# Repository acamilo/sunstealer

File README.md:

## SunStealer

Sunstealer is a 15 watt single color (rs485) networked LED strip built using a LT34781 driver and a PIC32MX110F016B. These strips are intended to be used to build larger LED panels with each strip covering a specific wavelength.

The goal is to be able to control the amount of light received by plants at each of these wavelengths and attempt to replicate some of the existing studies on type of light and it's affect on vegetative growth and fruiting.

There will be 5 variants of the strip each populated with LEDs targeting te following wavelengths (439,469,642,667,740) initially with the following ratios (1,1,2,2,1) This should make 1 105w LED light for hydro/aquaponics.

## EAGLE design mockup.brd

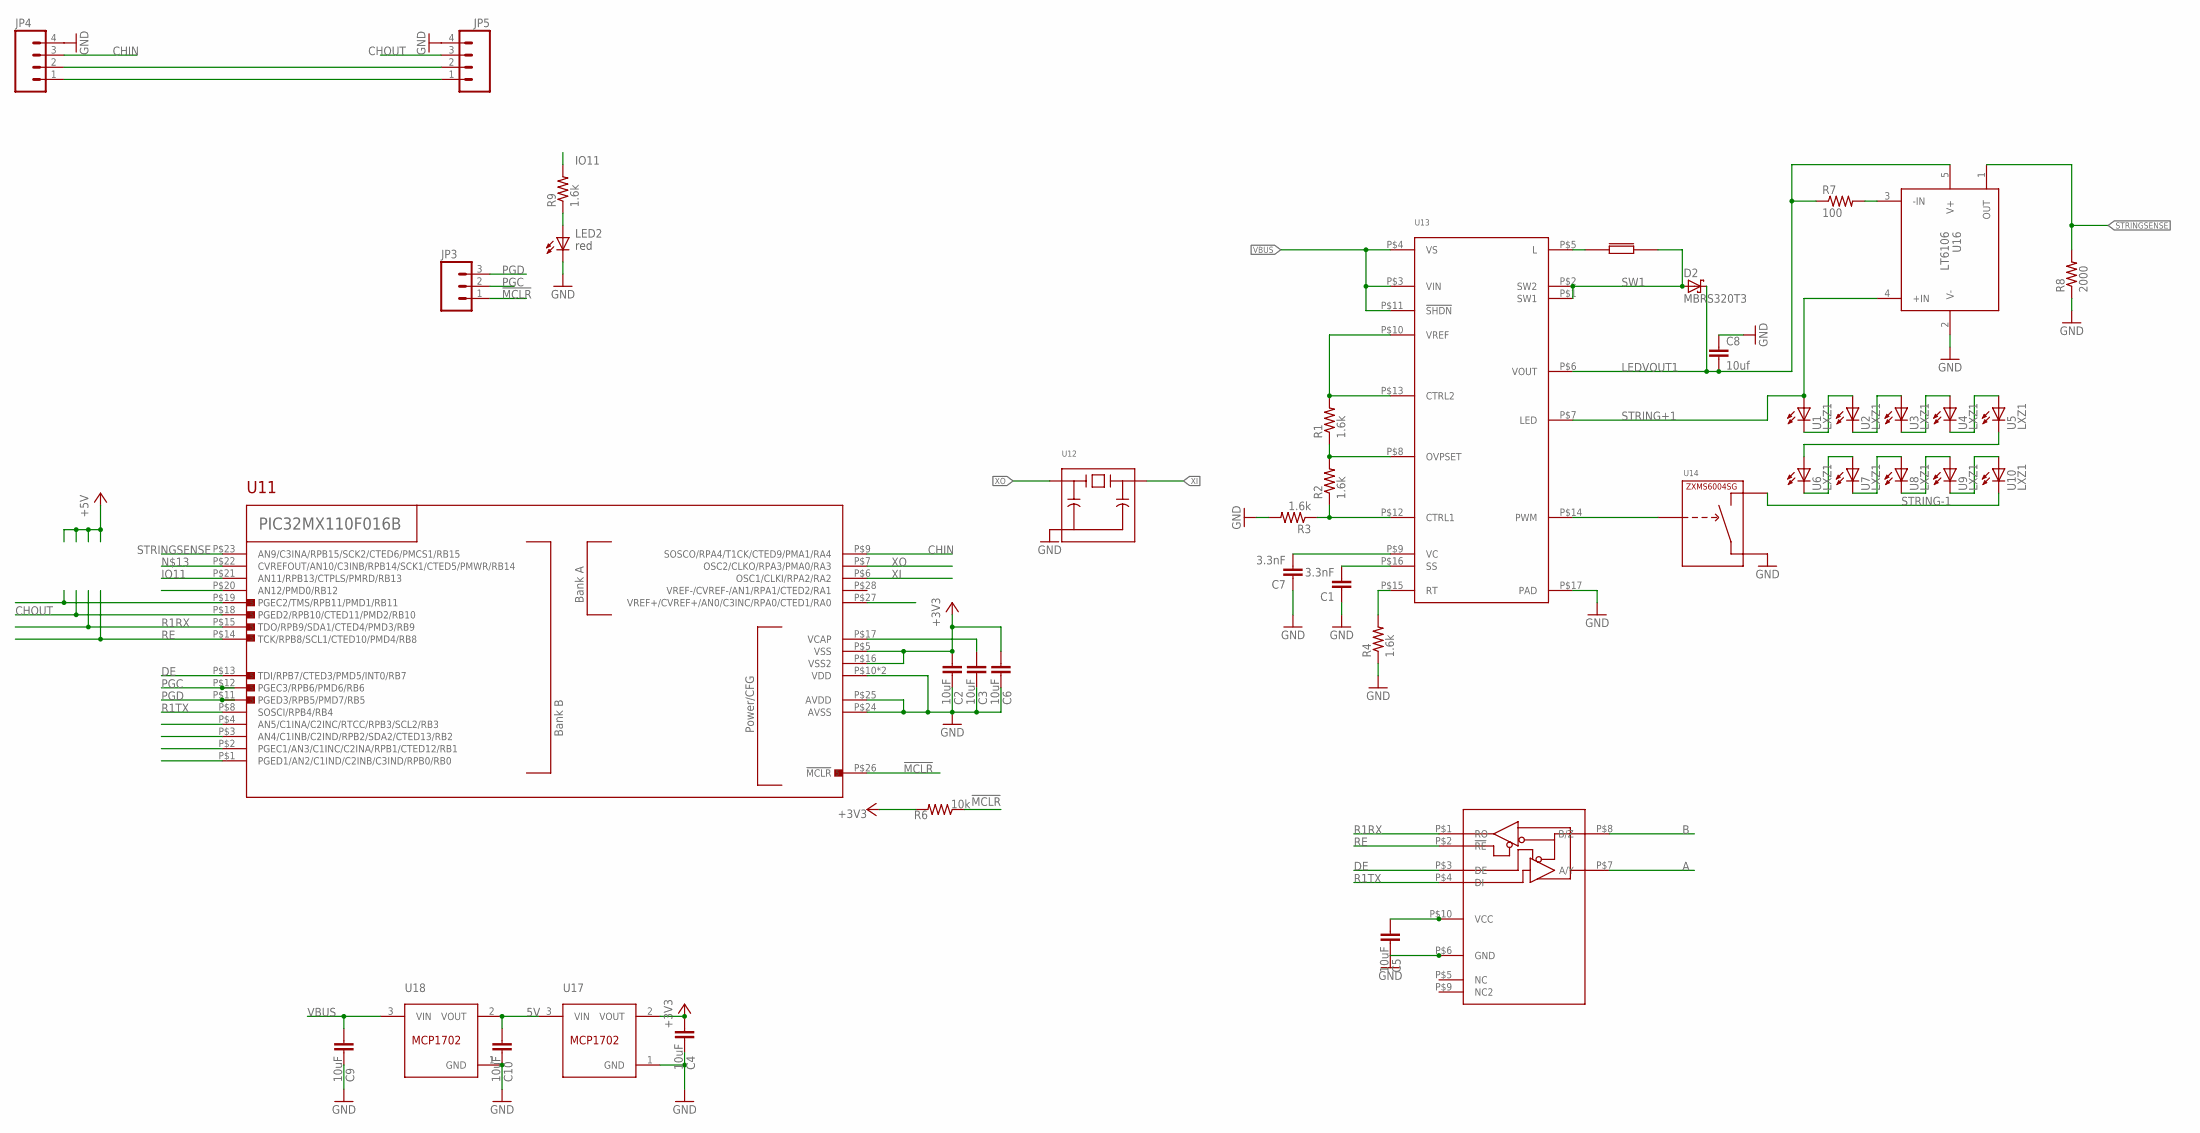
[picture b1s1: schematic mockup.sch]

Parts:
C1, C7: 3.3nF; 0402-CAP
C2, C4, C5, C6, C10: 10uF; 0402-CAP; PART# LMK212BJ106KG-T
C3, C9: 10uF; 0805; PART# LMK212BJ106KG-T
C8: 10uf; 1206
D2: MBRS320T3; SMC
JP3: M031X03_NO_SILK; 1X03_NO_SILK
JP4, JP5: M041X04_NO_SILK; 1X04_NO_SILK
LED2: LS L29K-G1J2-1-Z; LED-0603
R1, R2, R3, R4, R9: 1.6k; 0402-RES
R6: 10k; 0402-RES
R7: 100; 0402-RES
R8: 2000; 0402-RES
U1, U2, U3, U4, U5, U6, U7, U8, U9, U10: LXZ1
U11: PIC32MX110QFN; 28-QFN
U12: CSTCE
U13: 34781F; TSSOP16
U14: ZXMS6004SG; SOT223
U15: ISL3159E; DFN10
U16: LT6106; 5-LEAD-TSOT-23
U17, U18: MCP1702T; SOT23
U$27: 74404064068

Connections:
5V: C5.1, C10.1, U15.P$10 (VCC), U17.3 (VIN), U18.2 (VOUT)
!MCLR: JP3.1, R6.1, U11.P$26 (!MCLR)
+3V3: C2.1, C4.1, C6.1, R6.2, U11.P$5 (VSS), U11.P$16 (VSS2), U17.2 (VOUT)
A: JP4.1, JP5.1, U15.P$7 (A/Y)
B: JP4.2, JP5.2, U15.P$8 (B/Z)
CHIN: JP4.3, U11.P$9 (SOSCO/RPA4/T1CK/CTED9/PMA1/RA4)
CHOUT: JP5.3, U11.P$18 (PGED2/RPB10/CTED11/PMD2/RB10)
CONFIG: U11.P$27 (VREF+/CVREF+/AN0/C3INC/RPA0/CTED1/RA0)
DE: U11.P$13 (TDI/RPB7/CTED3/PMD5/INT0/RB7), U15.P$3 (DE)
GND: C1.1, C2.2, C3.2, C4.2, C5.2, C6.2, C7.1, C8.1, C9.2, C10.2, JP4.4, JP5.4, LED2.C, R3.2, R4.1, R8.1, U11.P$10 (VDD), U11.P$24 (AVSS), U11.P$25 (AVDD), U11.P$29 (VDD), U12.2, U13.P$17 (PAD), U14.3 (S), U14.4 (S), U15.P$6 (GND), U16.2 (V-), U17.1 (GND), U18.1 (GND)
IO4: U11.P$20 (AN12/PMD0/RB12)
IO6: U11.P$4 (AN5/C1INA/C2INC/RTCC/RPB3/SCL2/RB3)
IO7: U11.P$3 (AN4/C1INB/C2IND/RPB2/SDA2/CTED13/RB2)
IO8: U11.P$2 (PGEC1/AN3/C1INC/C2INA/RPB1/CTED12/RB1)
IO9: U11.P$1 (PGED1/AN2/C1IND/C2INB/C3IND/RPB0/RB0)
IO11: R9.2, U11.P$21 (AN11/RPB13/CTPLS/PMRD/RB13)
L1: U13.P$5 (L), U$27.P$1
LEDVOUT1: C8.2, D2.C, R7.1, U13.P$6 (VOUT), U16.5 (V+)
unnamed: LED2.A, R9.1
unnamed: R2.1, R3.1, U13.P$12 (CTRL1)
unnamed: R1.1, R2.2, U13.P$8 (OVPSET)
unnamed: C3.1, U11.P$17 (VCAP)
unnamed: R1.2, U13.P$10 (VREF), U13.P$13 (CTRL2)
unnamed: R4.2, U13.P$15 (RT)
unnamed: C7.2, U13.P$9 (VC)
unnamed: C1.2, U13.P$16 (SS)
unnamed: U11.P$22 (CVREFOUT/AN10/C3INB/RPB14/SCK1/CTED5/PM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), U13.P$14 (PWM), U14.1 (IN)
unnamed: U1.K (C), U2.A
unnamed: U2.K (C), U3.A
unnamed: U3.K (C), U4.A
unnamed: U4.K (C), U5.A
unnamed: U5.K (C), U6.A
unnamed: U6.K (C), U7.A
unnamed: U7.K (C), U8.A
unnamed: U8.K (C), U9.A
unnamed: U9.K (C), U10.A
unnamed: R7.2, U16.3 (-IN)
PGC: JP3.2, U11.P$12 (PGEC3/RPB6/PMD6/RB6)
PGD: JP3.3, U11.P$11 (PGED3/RPB5/PMD7/RB5)
R1RX: U11.P$15 (TDO/RPB9/SDA1/CTED4/PMD3/RB9), U15.P$1 (RO)
R1TX: U11.P$8 (SOSCI/RPB4/RB4), U15.P$4 (DI)
RE: U11.P$14 (TCK/RPB8/SCL1/CTED10/PMD4/RB8), U15.P$2 (!RE)
SERVO1: U11.P$19 (PGEC2/TMS/RPB11/PMD1/RB11)
STRING+1: U1.A, U13.P$7 (LED), U16.4 (+IN)
STRING-1: U10.K (C), U14.2 (D)
STRINGSENSE: R8.2, U11.P$23 (AN9/C3INA/RPB15/SCK2/CTED6/PMCS1/RB15), U16.1 (OUT)
SW1: D2.A, U13.P$1 (SW1), U13.P$2 (SW2), U$27.P$2
VBUS: C9.1, U13.P$3 (VIN), U13.P$4 (VS), U13.P$11 (!SHDN), U18.3 (VIN)
XI: U11.P$6 (OSC1/CLKI/RPA2/RA2), U12.3
XO: U11.P$7 (OSC2/CLKO/RPA3/PMA0/RA3), U12.1

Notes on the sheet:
red

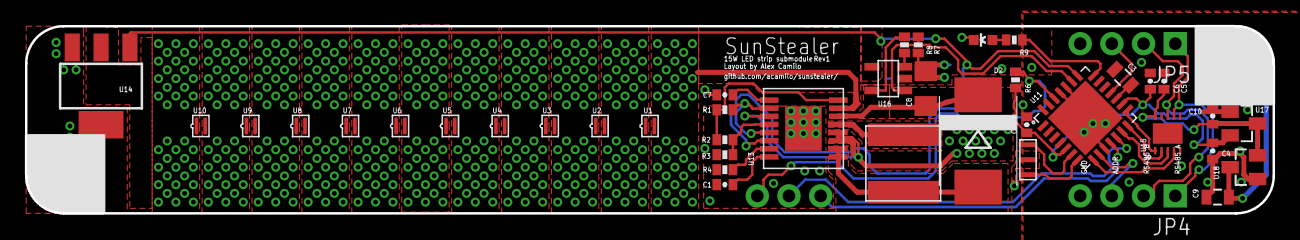
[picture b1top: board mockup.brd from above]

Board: 2 copper layers, 100.0 x 15.0 mm, 42 parts (0 on the bottom side), 43 nets.

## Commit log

2015-07-20 board layout done
2015-07-20 cleaned up silk
2015-07-20 added image
2015-07-25 Update README.md
    fixed spelling

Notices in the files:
parts and their libraries:
SparkFun-Connectors: Licensing: Creative Commons ShareAlike 4.0 International - https://creativecommons.org/licenses/by-sa/4.0
SparkFun-Passives: Licensing: CC v3.0 Share-Alike You are welcome to use this library for commercial purposes.
